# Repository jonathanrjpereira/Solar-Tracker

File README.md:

# Solar-Tracker
Single Axis Solar Tracker without Microcontroller

|Parts|Specification|Quantity|
|--|--|--|
|L293D|Quadruple Half-H Drivers|1|
|LM324|Low-Power, Quad-Operational Amplifiers|1|
|HEF4081B|Quad 2-input AND gate|1|
|7805|5V Linear Regulator|1|
|Limit Switch|SPDT|2|
|LDR|Size & resistance varies according to your requirement|2|
|Potentiometers|5K Ohm|3|
|Resistors|1K Ohm|2|
|Diode|IN4001|2|
|LED|2V|2|
|DC Motor|9V or 12V|1|
|Power Supply|9V or 12V|1|
|Solar Panel|Optional|1|

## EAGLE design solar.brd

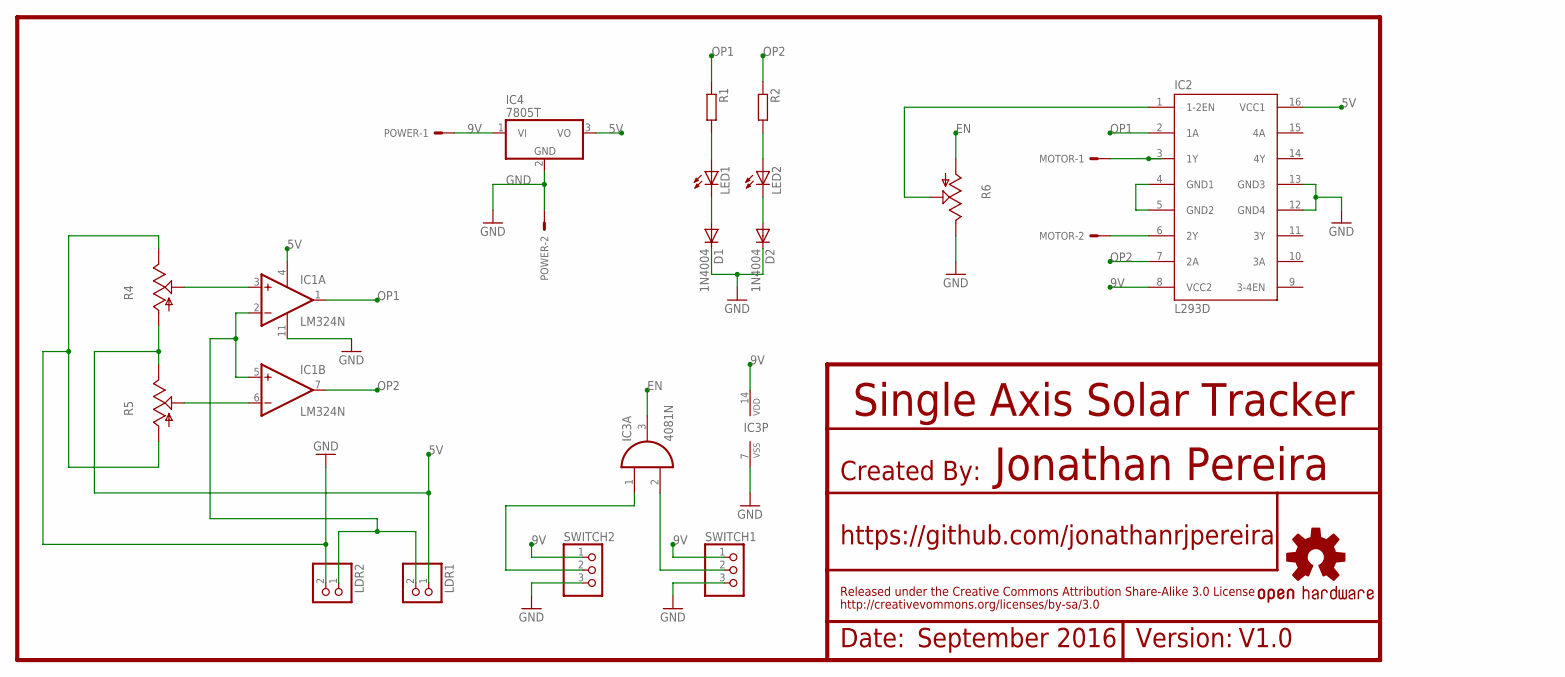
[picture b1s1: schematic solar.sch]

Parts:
D1, D2: 1N4004; DO41-10
IC1: LM324N; DIL14
IC2: L293D; DIL16
IC3: 4081N; DIL14
IC4: 7805T; TO220H
LDR1, LDR2: PINHD-1X2; 1X02
LED1, LED2: LED5MM
LOGO1: OSHW-LOGOL-COPPER; OSHW-LOGO-L_COPPER
MOTOR: KK-156-2
POWER: KK-156-2
R1, R2: R-EU_0204/7; 0204/7
R4, R5, R6: TRIM_US-CA6V; CA6V
SWITCH1, SWITCH2: PINHD-1X3; 1X03

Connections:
5V: IC1.4 (V+), IC2.16 (VCC1), IC4.3 (VO), LDR1.1, R4.A, R5.E
9V: IC2.8 (VCC2), IC3.14 (VDD), IC4.1 (VI), POWER.1, SWITCH1.1, SWITCH2.1
EN: IC3.3 (O), R6.A
GND: D1.C, D2.C, IC1.11 (V-), IC2.12 (GND4), IC2.13 (GND3), IC3.7 (VSS), IC4.2 (GND), LDR2.2, POWER.2, R4.E, R5.A, R6.E, SWITCH1.3, SWITCH2.3
unnamed: IC2.3 (1Y), MOTOR.1
unnamed: IC2.6 (2Y), MOTOR.2
unnamed: IC2.4 (GND1), IC2.5 (GND2)
unnamed: IC2.1 (1-2EN), R6.S
unnamed: IC3.1 (I0), SWITCH2.2
unnamed: IC3.2 (I1), SWITCH1.2
unnamed: IC1.2 (-IN), IC1.5 (+IN), LDR1.2, LDR2.1
unnamed: IC1.3 (+IN), R4.S
unnamed: IC1.6 (-IN), R5.S
unnamed: LED1.A, R1.2
unnamed: LED2.A, R2.2
unnamed: D2.A, LED2.K (C)
unnamed: D1.A, LED1.K (C)
OP1: IC1.1 (OUT), IC2.2 (1A), R1.1
OP2: IC1.7 (OUT), IC2.7 (2A), R2.1

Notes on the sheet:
Date:
Version:
September 2016
V1.0
Single Axis Solar Tracker
Jonathan Pereira
Created By:
https://github.com/jonathanrjpereira
Released under the Creative Commons Attribution Share-Alike 3.0 License
http://creativevommons.org/licenses/by-sa/3.0

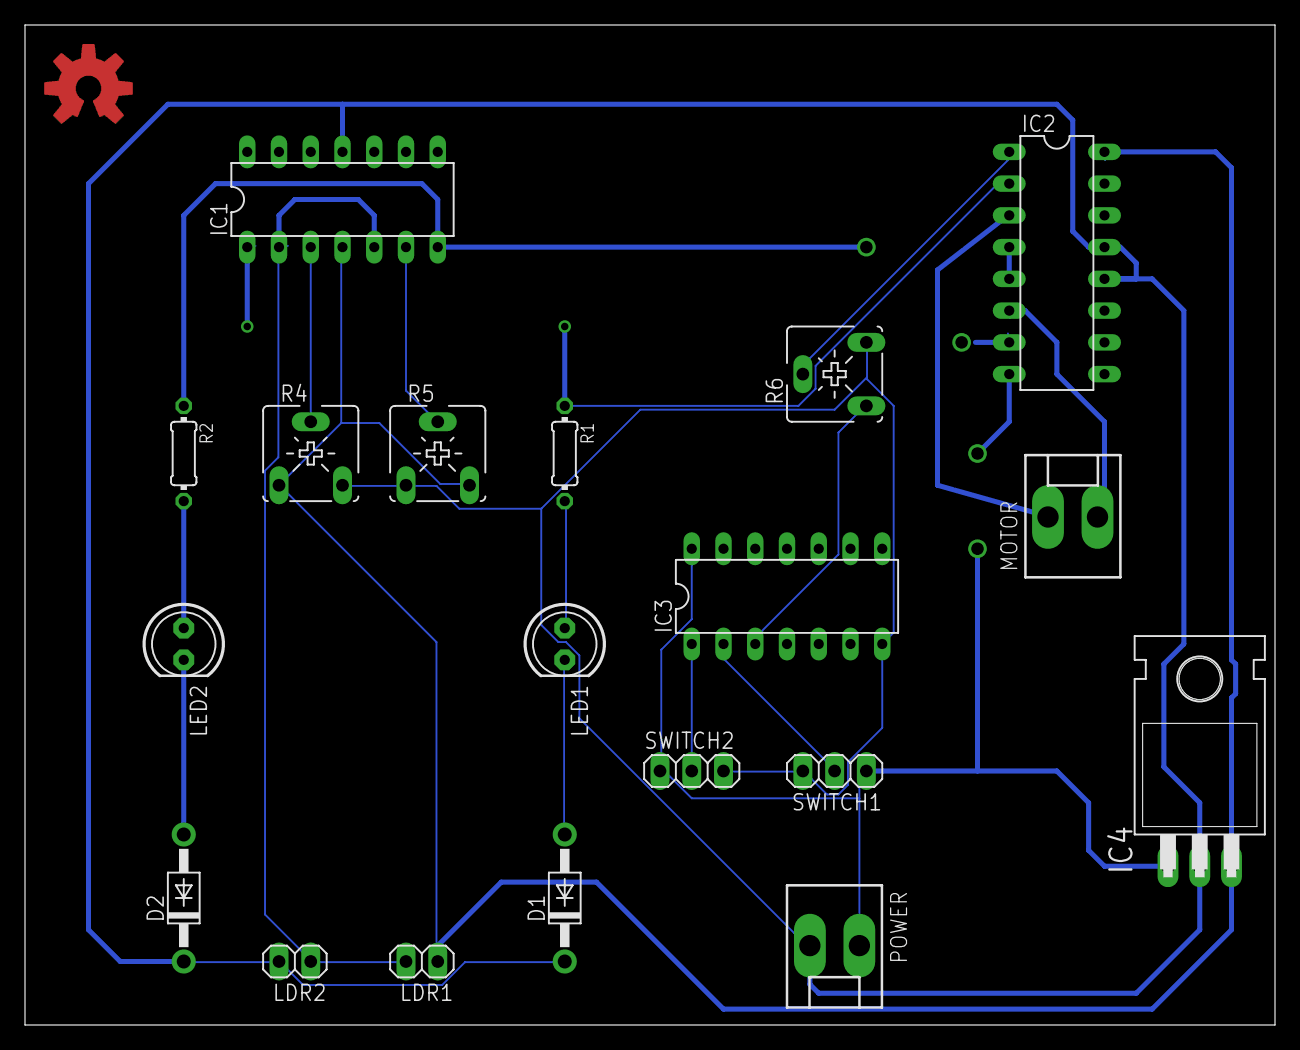
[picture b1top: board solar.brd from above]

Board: 2 copper layers, 100.0 x 80.0 mm, 20 parts (0 on the bottom side), 19 nets.

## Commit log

2018-06-22 Eagle File
2018-06-22 Eagle Schematic
2018-06-22 Eagle Board
2018-06-22 Schematic & Board Pictures
2018-06-22 Parts List
2018-08-01 Images
2018-09-03 Git Ignore

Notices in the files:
parts and their libraries:
SparkFun-Aesthetics: Licensing: Creative Commons ShareAlike 4.0 International - https://creativecommons.org/licenses/by-sa/4.0
